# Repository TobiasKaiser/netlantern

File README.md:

netlantern
==========

Prototype:

Dimensions
----------

PCB dimensions: 45 x 90 x 1.6 mm

Diffusor dimensions: 54 x 90 x 3 mm

LED calculation
---------------

8 rows by 4 columns of WS2812B LEDs = 32 LEDs per PCB

6 PCBs * 32 LEDs = 192 LEDs total

192 * 15 mA (worst case current consumption at 3.7 V supply voltage)
= 2.88 A total current

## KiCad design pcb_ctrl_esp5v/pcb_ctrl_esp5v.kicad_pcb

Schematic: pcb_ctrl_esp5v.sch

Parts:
C1, C3, C4, C6, C7, C8, C9, C10: 100n; C_0805_2012Metric_Pad1.15x1.40mm_HandSolder
C2: 10u; C_0805_2012Metric_Pad1.15x1.40mm_HandSolder
C5: 4.7u; C_0805_2012Metric_Pad1.15x1.40mm_HandSolder
J1: USB_B_Micro; USB_Micro-B_Molex-105017-0001
J2: Barrel_Jack; BarrelJack_CUI_PJ-102AH_Horizontal
J3: Conn_02x10_Odd_Even; PinSocket_2x10_P2.54mm_Vertical
J4: Conn_01x03; PinSocket_1x03_P2.54mm_Vertical
Q1, Q2: S8050 SOT-23; SOT-23_Handsoldering
R1, R2, R4: 10k; R_0805_2012Metric_Pad1.15x1.40mm_HandSolder
R3: 4.7k; R_0805_2012Metric_Pad1.15x1.40mm_HandSolder
R5: 121; R_0805_2012Metric_Pad1.15x1.40mm_HandSolder
R6: 200; R_0805_2012Metric_Pad1.15x1.40mm_HandSolder
SW1, SW2: SW_SPST; SW_SPST_PTS645
U1: ESP32-WROOM
U2: LM1117-ADJ; SOT-223-3_TabPin2
U3: FT232RL; SSOP-28_5.3x10.2mm_P0.65mm
U4: 74HC00; SOIC-14_3.9x8.7mm_P1.27mm

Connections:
+3V3: C6.1, C10.2, J3.1, R5.1, U1.2, U2.2
+5V: C2.1, C3.2, C4.2, C5.2, C9.1, J2.1, J3.2, J4.1, U2.3, U3.20, U4.14 (VCC)
/DOUT: J4.2, U4.6
/DOUT_33: U1.36, U4.1, U4.2
/DTR: Q2.2, R1.2, U3.2
/EN: C8.1, J3.17, Q2.3, SW2.2, U1.3
/IO0: C7.1, J3.18, Q1.3, SW1.2, U1.25
/IO12: J3.8, U1.14
/IO13: J3.6, U1.16
/IO14: J3.10, U1.13
/IO25: J3.13, U1.10
/IO26: J3.14, U1.11
/IO27: J3.12, U1.12
/IO32: J3.9, U1.8
/IO33: J3.11, U1.9
/IO34: J3.5, U1.6
/IO35: J3.7, U1.7
/RTS: Q1.2, R2.2, U3.3
/RXD0: J3.15, U1.34, U3.5
/SENSOR_VN: J3.4, U1.5
/SENSOR_VP: J3.3, U1.4
/TXD0: J3.16, U1.35, U3.1
GND: C1.2, C2.2, C3.1, C4.1, C5.1, C6.2, C7.2, C8.2, C9.2, C10.1, J1.5, J2.2, J3.19, J3.20, J4.3, R4.2, R6.2, SW1.1, SW2.1, U1.1, U1.15, U1.38, U1.39, U3.7, U3.18, U3.21, U3.25, U3.26, U4.7 (GND)
unnamed: C1.1, U3.4, U3.17
unnamed: J1.1, R3.2
unnamed: J1.2, U3.16
unnamed: J1.3, U3.15
unnamed: Q1.1, R1.1
unnamed: Q2.1, R2.1
unnamed: R3.1, R4.1, U3.19
unnamed: R5.2, R6.1, U2.1
unnamed: U4.3, U4.4, U4.5

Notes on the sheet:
USB to UART
ESP32 Controller
Setup switches
Connectors
5 V Input + 3.3 V Reg
Level shift

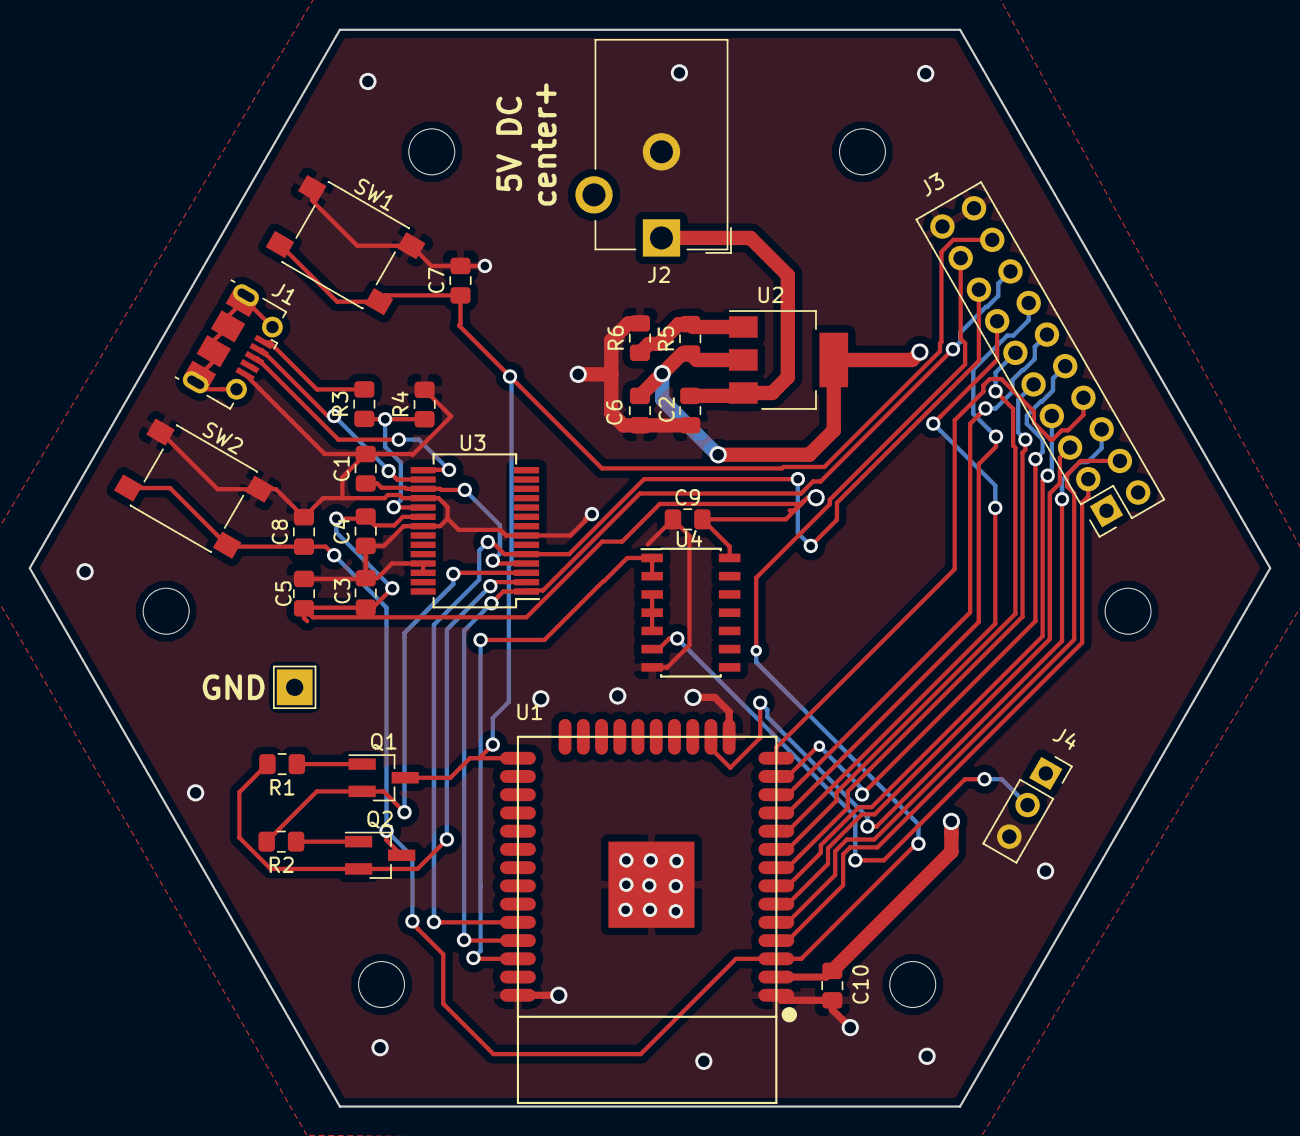
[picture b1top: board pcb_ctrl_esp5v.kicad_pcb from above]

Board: 2 copper layers, 86.4 x 75.0 mm, 28 parts (0 on the bottom side), 32 nets.

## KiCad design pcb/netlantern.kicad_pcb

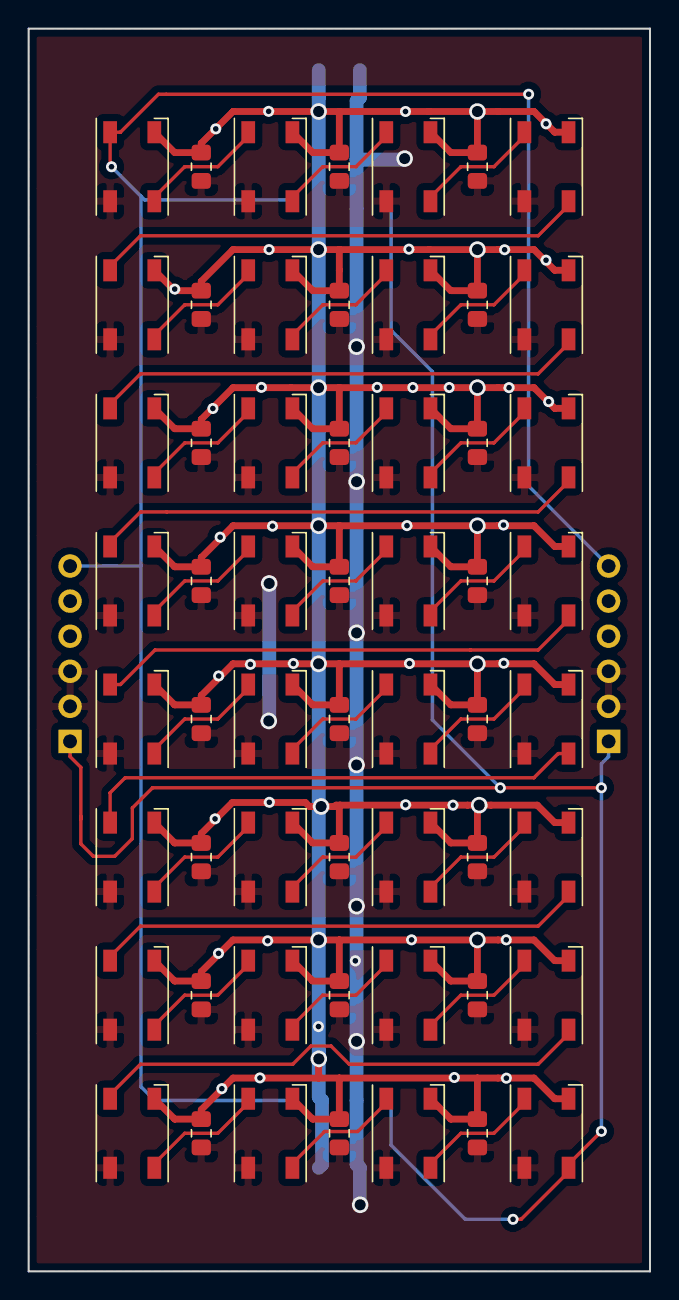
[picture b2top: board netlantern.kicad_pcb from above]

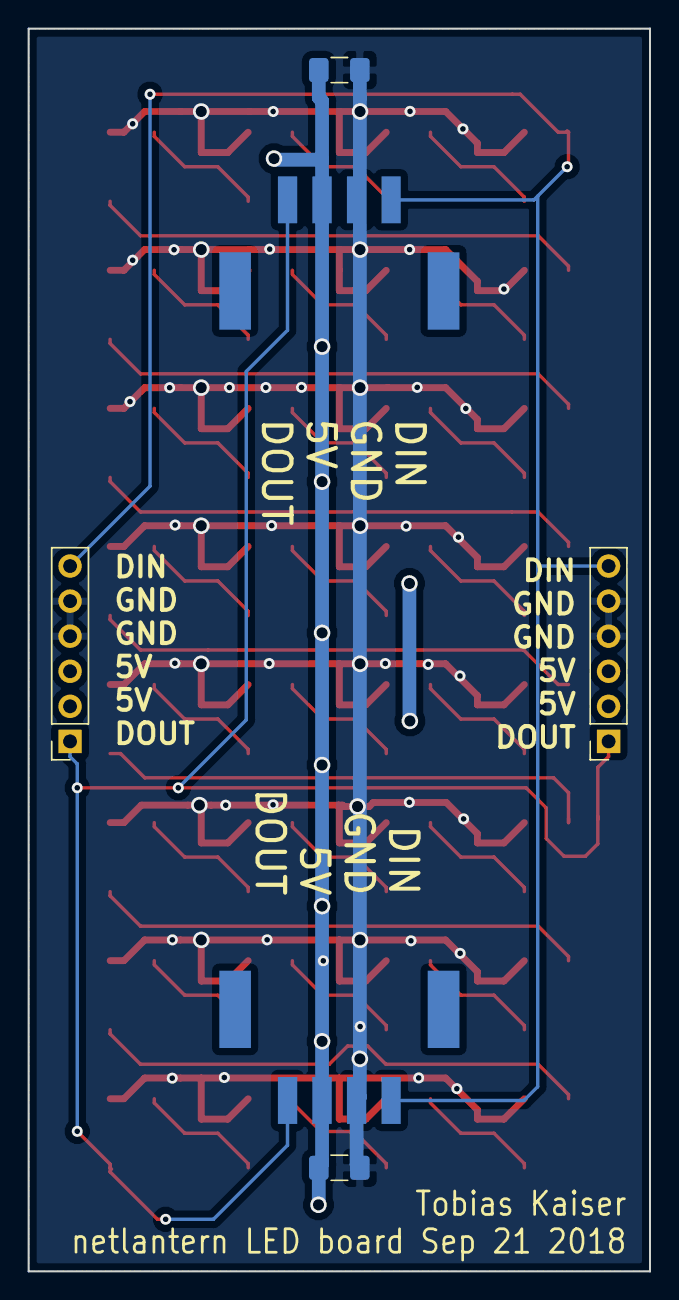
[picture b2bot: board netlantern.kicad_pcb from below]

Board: 2 copper layers, 45.0 x 90.0 mm, 62 parts (6 on the bottom side), 35 nets.

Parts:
C1, C2, C3, C4, C5, C6, C7, C8, C9, C10, C11, C12, C13, C14, C15, C16, C17, C18, C19, C20, C21, C22, C23, C24: 100n; C_0805_2012Metric_Pad1.15x1.40mm_HandSolder
C25, C26: 10u; C_1206_3216Metric_Pad1.42x1.75mm_HandSolder
D1, D2, D3, D4, D5, D6, D7, D8, D9, D10, D11, D12, D13, D14, D15, D16, D17, D18, D19, D20, D21, D22, D23, D24, D25, D26, D27, D28, D29, D30, D31, D32: WS2812B; LED_WS2812B-PLCC4
J1, J4: Screw_Terminal_01x04; TerminalBlock_Phoenix_PTSM-0,5-4-2,5-V-SMD_1x04_P2.50mm_Hor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
J2, J3: Conn_01x06; PinSocket_1x06_P2.54mm_Vertical

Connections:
+5V: C1.1, C2.1, C3.1, C4.1, C5.1, C6.1, C7.1, C8.1, C9.1, C10.1, C11.1, C12.1, C13.1, C14.1, C15.1, C16.1, C17.1, C18.1, C19.1, C20.1, C21.1, C22.1, C23.1, C24.1, C25.1, C26.1, D1.1, D2.1, D3.1, D4.1, D5.1, D6.1, D7.1, D8.1, D9.1, D10.1, D11.1, D12.1, D13.1, D14.1, D15.1, D16.1, D17.1, D18.1, D19.1, D20.1, D21.1, D22.1, D23.1, D24.1, D25.1, D26.1, D27.1, D28.1, D29.1, D30.1, D31.1, D32.1, J1.2, J2.2, J2.3, J3.2, J3.3, J4.3
/DIN: D1.4, J1.4, J2.6, J3.6, J4.1
/DOUT: D32.2, J1.1, J2.1, J3.1, J4.4
GND: C1.2, C2.2, C3.2, C4.2, C5.2, C6.2, C7.2, C8.2, C9.2, C10.2, C11.2, C12.2, C13.2, C14.2, C15.2, C16.2, C17.2, C18.2, C19.2, C20.2, C21.2, C22.2, C23.2, C24.2, C25.2, C26.2, D1.3, D2.3, D3.3, D4.3, D5.3, D6.3, D7.3, D8.3, D9.3, D10.3, D11.3, D12.3, D13.3, D14.3, D15.3, D16.3, D17.3, D18.3, D19.3, D20.3, D21.3, D22.3, D23.3, D24.3, D25.3, D26.3, D27.3, D28.3, D29.3, D30.3, D31.3, D32.3, J1.3, J2.4, J2.5, J3.4, J3.5, J4.2
unnamed: D1.2, D2.4
unnamed: D2.2, D3.4
unnamed: D3.2, D4.4
unnamed: D4.2, D5.4
unnamed: D5.2, D6.4
unnamed: D6.2, D7.4
unnamed: D7.2, D8.4
unnamed: D8.2, D9.4
unnamed: D10.2, D11.4
unnamed: D9.2, D10.4
unnamed: D11.2, D12.4
unnamed: D12.2, D13.4
unnamed: D13.2, D14.4
unnamed: D14.2, D15.4
unnamed: D15.2, D16.4
unnamed: D16.2, D17.4
unnamed: D17.2, D18.4
unnamed: D18.2, D19.4
unnamed: D19.2, D20.4
unnamed: D20.2, D21.4
unnamed: D21.2, D22.4
unnamed: D22.2, D23.4
unnamed: D23.2, D24.4
unnamed: D24.2, D25.4
unnamed: D25.2, D26.4
unnamed: D26.2, D27.4
unnamed: D27.2, D28.4
unnamed: D28.2, D29.4
unnamed: D29.2, D30.4
unnamed: D30.2, D31.4
unnamed: D31.2, D32.4

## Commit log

2018-08-27 added more design info
2018-08-28 working on schematic
2018-08-31 working on layout
2018-08-31 working on stuff
2018-09-20 decided to do in parts - led board ready to send
2018-09-21 added more connectors
2018-12-16 working on ctrl test pcb
2018-12-16 schematic more or less done
2018-12-17 working on footprint association
2019-02-10 basic part selection for new ctrl board
2019-02-10 working on ctrl pcb
2019-02-10 pretty much ready to order now, checks required
2019-02-11 ERC clean
2019-02-11 remove temporary files
2019-02-11 DRC clean - ordering this now
